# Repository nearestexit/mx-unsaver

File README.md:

# mx-unsaver

Custom keyboard and numpad inspired by vintage Cherry keyboards and the [IBM "Unsaver"](https://sharktastica.co.uk/topics/keyboard-dictionary/unsaver).
Designed in Onshape and KiCad.
Powered by [QMK](https://github.com/qmk/qmk_firmware).

## Overview
- Side profile and shape inspired by the Cherry G80-5700 and G80-1800
- PCB Top-Mount
- Integrated USB Hub with 1x USB-C Upstream port and 2x USB-C and 2x USB-A Downstream ports
- Brass through-weight

**Case Source (Onshape):** https://cad.onshape.com/documents/1d9e79a61d42e7395c429f47/w/28912f958105e1c831f67a9e/e/537bd51b2d234361e6d6eea3

## PCB
The PCB supports ISO and ANSI. Unfortunately, due to an oversight, the Case only supports ANSI enter. It could be relatively easily modified to support ISO enter.
I ordered single bare PCBs from EuroCircuits and OSHPark and hand-soldered the components, so I do not have JLCPCB production files available.

**Important: The PCB has the words "Made In Germany" printed on it. This is because it was actually manufactured in Germany. If you choose to have it manufactured in China, please remove this logo from the PCB.**

## Bill of Materials

| Item  | Quantity | Link |
| ------------- | ------------- | ------------- | 
| M2x4x3mm Hex Standoff | 2 | https://www.ebay.com/itm/355663469861?var=624766479032 |
| M2x3x4mm Wafer head Screw | 2 | https://www.ebay.com/itm/355676691340?var=624776776427 |
| Feet | 8 | https://cannonkeys.com/products/akb-feet |
| M2.5x8mm BHCS | 57 | https://mcmaster.com/92095A459 |
| M2.5x6mm SHCS | 14 | https://mcmaster.com/91292A010 |
| M2.5x10mm SHCS | 7 | https://mcmaster.com/91292A014 |
| M2.5x25mm SHCS | 6 | https://mcmaster.com/91292A036 |
| M2.5x20mm SHCS | 4 | https://mcmaster.com/91292A019 |
| M3x6mm Countersunk | 5 | https://mcmaster.com/92125A126 |
| M3x8mm Countersunk | 9 | https://mcmaster.com/92125A128 |
| 1:1 JST-SH Cable (50mm) | 3 | https://www.digikey.com/en/products/detail/adafruit-industries-llc/4210/10230021 |
| FPC Cable (50.8mm) | 1 | https://www.digikey.com/en/products/detail/molex/0151660207/3281088 |

## USB Hub
The USB Hub utilizes two [FE1.1S](https://www.digikey.ca/datasheets/production/1879844/1/FE1-1s-Datasheet.html) USB 2.0 HS Hub chips in series. It can deliver a total of 400mA downstream (the keyboard is assumed to use 100mA).

## Firmware

A QMK .bin file is provided for flashing, as well as QMK source files.

(The original Unsaver in this picture is not for sale.)

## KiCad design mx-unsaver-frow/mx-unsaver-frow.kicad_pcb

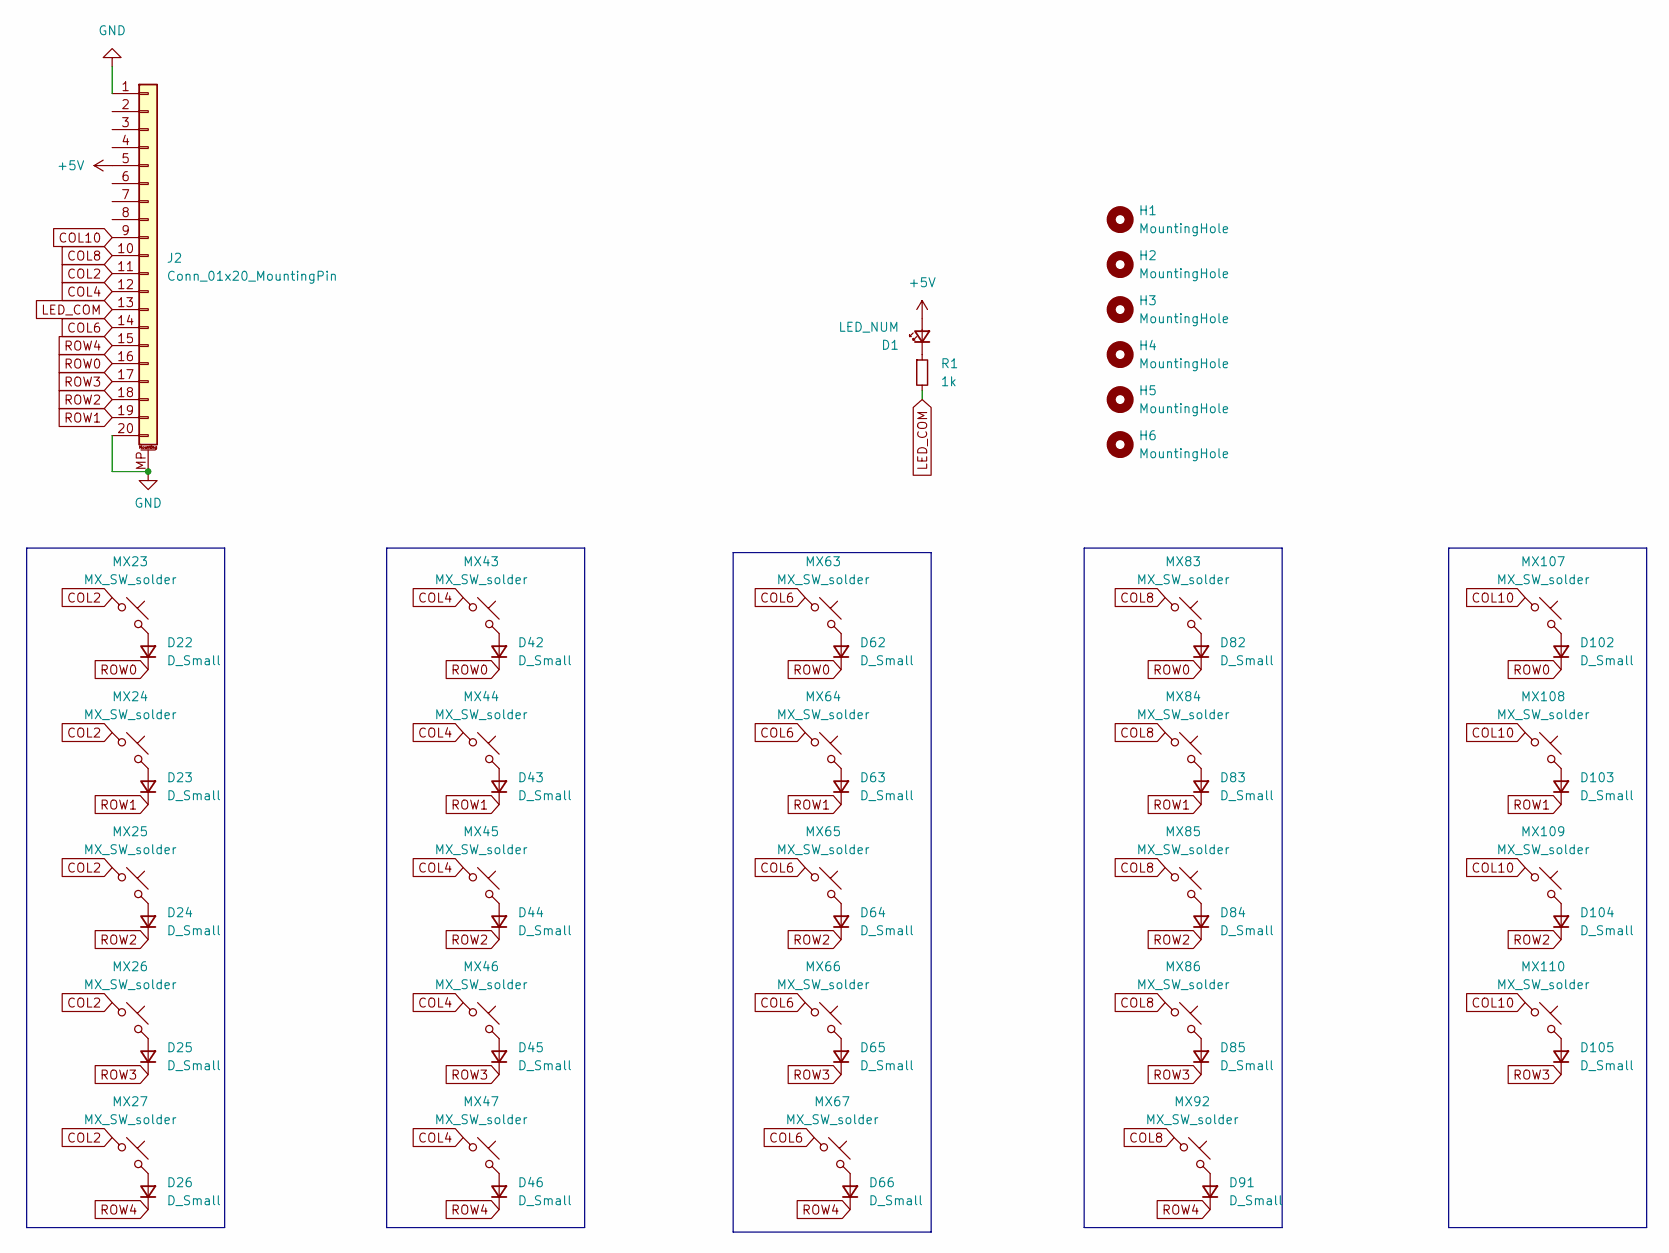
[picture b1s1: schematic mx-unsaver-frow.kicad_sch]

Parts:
D1: LED_NUM; LED_MX_3mm_Offset_Flipped; Digikey 67-1058-ND
D22, D23, D24, D25, D26, D42, D43, D44, D45, D46, D62, D63, D64, D65, D66, D82, D83, D84, D85, D91, D102, D103, D104, D105: D_Small; D_SOD-123_ShiftedSilkscreen; Digikey 1N4148W-FDICT-ND
H1, H2, H3, H4, H5, H6: MountingHole; MountingHole_2.7mm_M2.5
J2: Conn_01x20_MountingPin; CONN-SMD_20P-P0.50_10051922-2010ELF; Digikey 609-10051922-2010ELFCT-ND
MX23, MX24, MX25, MX26, MX27, MX43, MX44, MX45, MX46, MX47, MX63, MX64, MX65, MX66, MX67, MX83, MX84, MX85, MX86, MX92, MX107, MX108, MX109, MX110: MX_SW_solder; SW_MX_1u_PCBMount
R1: 1k; R_0805_2012Metric; Digikey P1.0KDACT-ND

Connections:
+5V: D1.2 (A), J2.5
COL2: J2.11, MX23.1, MX24.1, MX25.1, MX26.1, MX27.1
COL4: J2.12, MX43.1, MX44.1, MX45.1, MX46.1, MX47.1
COL6: J2.14, MX63.1, MX64.1, MX65.1, MX66.1, MX67.1
COL8: J2.10, MX83.1, MX84.1, MX85.1, MX86.1, MX92.1
COL10: J2.9, MX107.1, MX108.1, MX109.1, MX110.1
GND: J2.1, J2.20, J2.MP (MountPin)
LED_COM: J2.13, R1.2
unnamed: D1.1 (K), R1.1
unnamed: D22.2 (A), MX23.2
unnamed: D23.2 (A), MX24.2
unnamed: D24.2 (A), MX25.2
unnamed: D25.2 (A), MX26.2
unnamed: D26.2 (A), MX27.2
unnamed: D42.2 (A), MX43.2
unnamed: D43.2 (A), MX44.2
unnamed: D44.2 (A), MX45.2
unnamed: D45.2 (A), MX46.2
unnamed: D46.2 (A), MX47.2
unnamed: D62.2 (A), MX63.2
unnamed: D63.2 (A), MX64.2
unnamed: D64.2 (A), MX65.2
unnamed: D65.2 (A), MX66.2
unnamed: D66.2 (A), MX67.2
unnamed: D82.2 (A), MX83.2
unnamed: D83.2 (A), MX84.2
unnamed: D84.2 (A), MX85.2
unnamed: D85.2 (A), MX86.2
unnamed: D91.2 (A), MX92.2
unnamed: D102.2 (A), MX107.2
unnamed: D103.2 (A), MX108.2
unnamed: D104.2 (A), MX109.2
unnamed: D105.2 (A), MX110.2
ROW0: D22.1 (K), D42.1 (K), D62.1 (K), D82.1 (K), D102.1 (K), J2.16
ROW1: D23.1 (K), D43.1 (K), D63.1 (K), D83.1 (K), D103.1 (K), J2.19
ROW2: D24.1 (K), D44.1 (K), D64.1 (K), D84.1 (K), D104.1 (K), J2.18
ROW3: D25.1 (K), D45.1 (K), D65.1 (K), D85.1 (K), D105.1 (K), J2.17
ROW4: D26.1 (K), D46.1 (K), D66.1 (K), D91.1 (K), J2.15

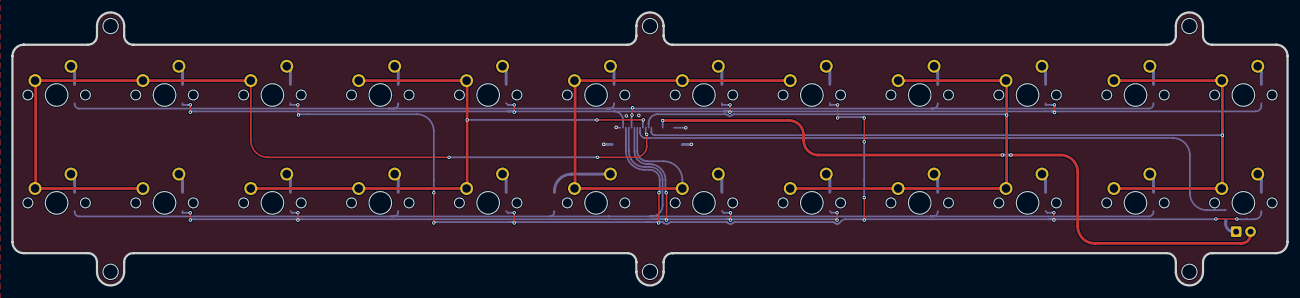
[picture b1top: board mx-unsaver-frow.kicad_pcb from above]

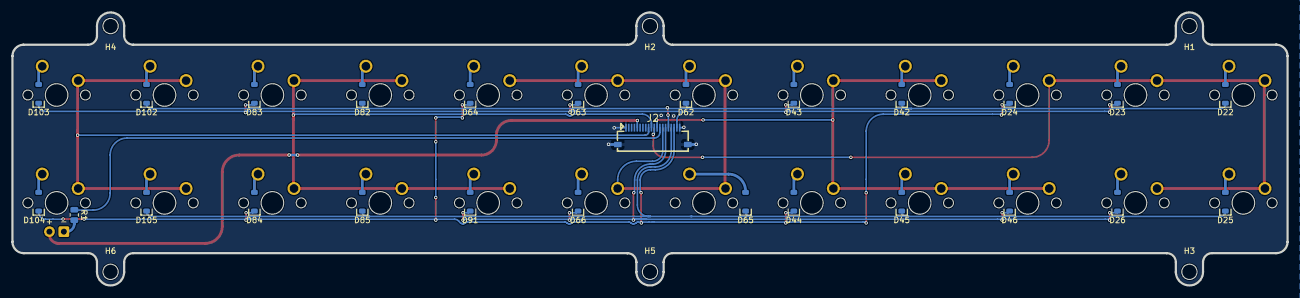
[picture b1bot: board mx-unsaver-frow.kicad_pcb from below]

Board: 2 copper layers, 225.2 x 48.2 mm, 57 parts (33 on the bottom side), 38 nets.

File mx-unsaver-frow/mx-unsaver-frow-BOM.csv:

"Reference","Value","Datasheet","Footprint","Qty","DNP","Digikey"
"D1","LED_NUM","~","mx-unsaver:LED_MX_3mm_Offset_Flipped","1","","67-1058-ND"
"D22,D23,D24,D25,D26,D42,D43,D44,D45,D46,D62,D63,D64,D65,D66,D82,D83,D84,D85,D91,D102,D103,D104,D105","D_Small","~","mx-unsaver:D_SOD-123_ShiftedSilkscreen","24","","1N4148W-FDICT-ND"
"J2","Conn_01x20_MountingPin","~","mx-unsaver:CONN-SMD_20P-P0.50_10051922-2010ELF","1","","609-10051922-2010ELFCT-ND"
"MX23,MX24,MX25,MX26,MX27,MX43,MX44,MX45,MX46,MX47,MX63,MX64,MX65,MX66,MX67,MX83,MX84,MX85,MX86,MX92,MX107,MX108,MX109,MX110","MX_SW_solder","~","mx-unsaver:SW_MX_1u_PCBMount","24","",""
"R1","1k","~","Resistor_SMD:R_0805_2012Metric","1","","P1.0KDACT-ND"

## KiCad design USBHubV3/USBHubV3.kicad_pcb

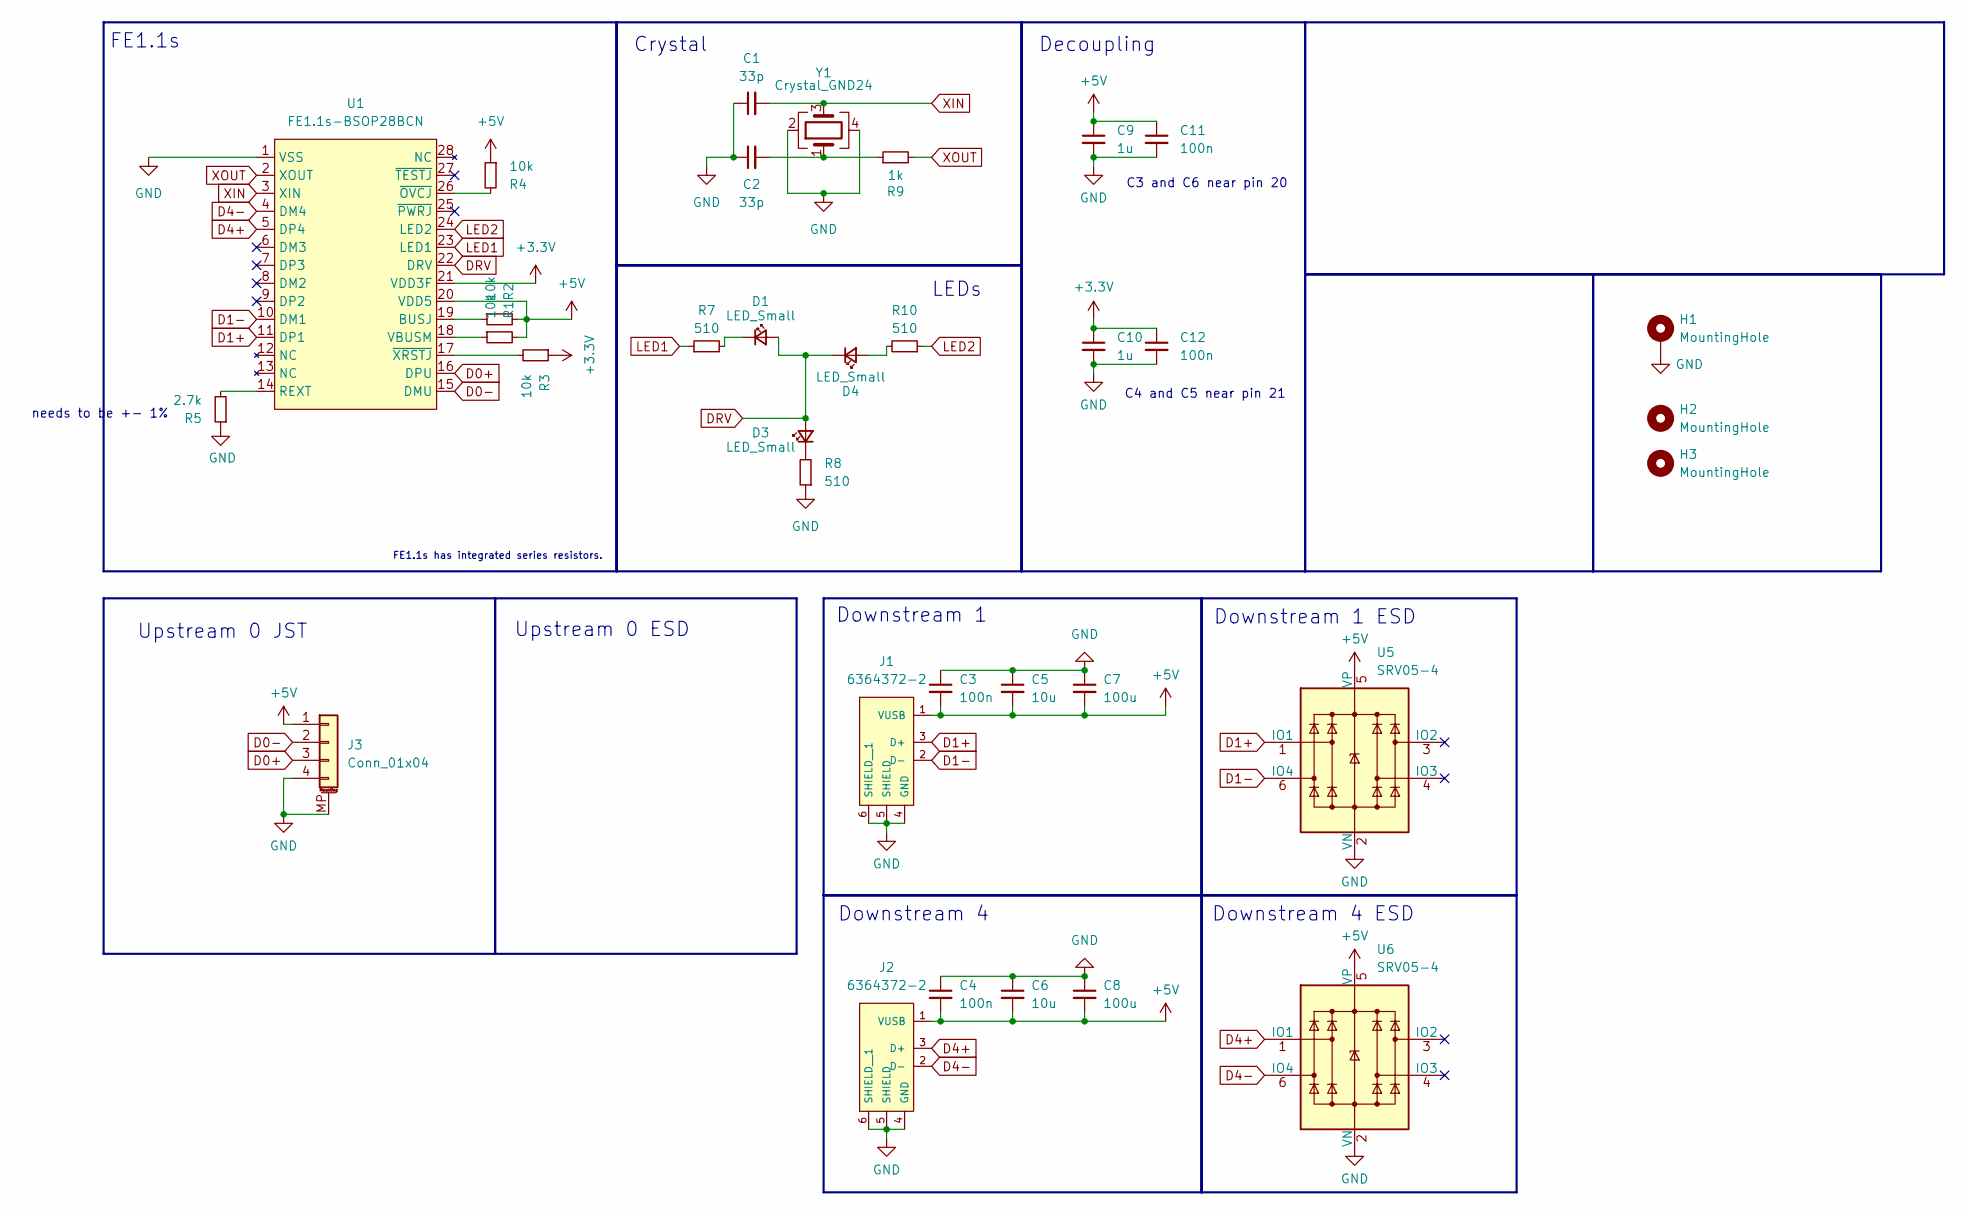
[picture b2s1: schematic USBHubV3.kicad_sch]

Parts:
C1, C2: 33p; C_0603_1608Metric; Digikey 1276-1070-1-ND
C3, C4, C11, C12: 100n; C_0603_1608Metric; Digikey 311-1088-1-ND
C5, C6: 10u; C_0603_1608Metric; Digikey 1276-1192-1-ND
C7, C8: 100u; C_1206_3216Metric; Digikey 490-GRM31CR60J107KEA8LCT-ND
C9, C10: 1u; C_0603_1608Metric; Digikey 1276-6524-1-ND
D1, D3, D4: LED_Small; LED_0603_1608Metric; Digikey 2007-BL-HJC36G-AV-TRBCT-ND
H1: MountingHole; MountingHole_2.7mm_M2.5_DIN965_Pad
H2, H3: MountingHole; MountingHole_2.7mm_M2.5
J1, J2: 6364372-2; TE_6364372-2; Digikey A122647-ND
J3: Conn_01x04; JST_SH_SM04B-SRSS-TB_1x04-1MP_P1.00mm_Horizontal; Digikey 455-SM04B-SRSS-TBCT-ND
R1, R2, R3, R4: 10k; R_0603_1608Metric; Digikey 311-10.0KHRCT-ND
R5: 2.7k; R_0603_1608Metric; Digikey RMCF0603FT2K70CT-ND
R7, R8, R10: 510; R_0603_1608Metric; Digikey RR08P510DCT-ND
R9: 1k; R_0603_1608Metric; Digikey RMCF0603FT1K00CT-ND
U1: FE1.1s-BSOP28BCN; SSOP-28_3.9x9.9mm_P0.635mm
U5, U6: SRV05-4; SOT-23-6-routable; Digikey 5399-SRV05-4CT-ND
Y1: Crystal_GND24; Crystal_SMD_3225-4Pin_3.2x2.5mm; Digikey XC1810CT-ND

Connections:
+3.3V: C10.1, C12.1, R3.1, U1.21 (VDD3F)
+5V: C3.2, C4.2, C5.2, C6.2, C7.2, C8.2, C9.1, C11.1, J1.1 (VUSB), J2.1 (VUSB), J3.1, R1.2, R2.2, R4.1, U1.20 (VDD5), U5.5 (VP), U6.5 (VP)
D0+: J3.3, U1.16 (DPU)
D0-: J3.2, U1.15 (DMU)
D1+: J1.3 (D+), U1.11 (DP1), U5.1 (IO1)
D1-: J1.2 (D-), U1.10 (DM1), U5.6 (IO4)
D4+: J2.3 (D+), U1.5 (DP4), U6.1 (IO1)
D4-: J2.2 (D-), U1.4 (DM4), U6.6 (IO4)
DRV: D1.2 (A), D3.2 (A), D4.1 (K), U1.22 (DRV)
GND: C1.1, C2.1, C3.1, C4.1, C5.1, C6.1, C7.1, C8.1, C9.2, C10.2, C11.2, C12.2, H1.1, J1.4 (GND), J1.5 (SHIELD), J1.6 (SHIELD__1), J2.4 (GND), J2.5 (SHIELD), J2.6 (SHIELD__1), J3.4, J3.MP (MountPin), R5.1, R8.1, U1.1 (VSS), U5.2 (VN), U6.2 (VN), Y1.2, Y1.4
LED1: R7.1, U1.23 (LED1)
LED2: R10.1, U1.24 (LED2)
unnamed: C2.2, R9.1, Y1.1
unnamed: D1.1 (K), R7.2
unnamed: D3.1 (K), R8.2
unnamed: D4.2 (A), R10.2
unnamed: R2.1, U1.19 (BUSJ)
unnamed: R5.2, U1.14 (REXT)
unnamed: R1.1, U1.18 (VBUSM)
unnamed: R4.2, U1.26 (~OVCJ)
unnamed: R3.2, U1.17 (~XRSTJ)
XIN: C1.2, U1.3 (XIN), Y1.3
XOUT: R9.2, U1.2 (XOUT)

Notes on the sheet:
Upstream 0 JST
Decoupling
Upstream 0 ESD
Downstream 4
FE1.1s
C4 and C5 near pin 21
FE1.1s has integrated series resistors.
LEDs
Downstream 1
Downstream 1 ESD
C3 and C6 near pin 20
Crystal
needs to be +- 1%
Downstream 4 ESD

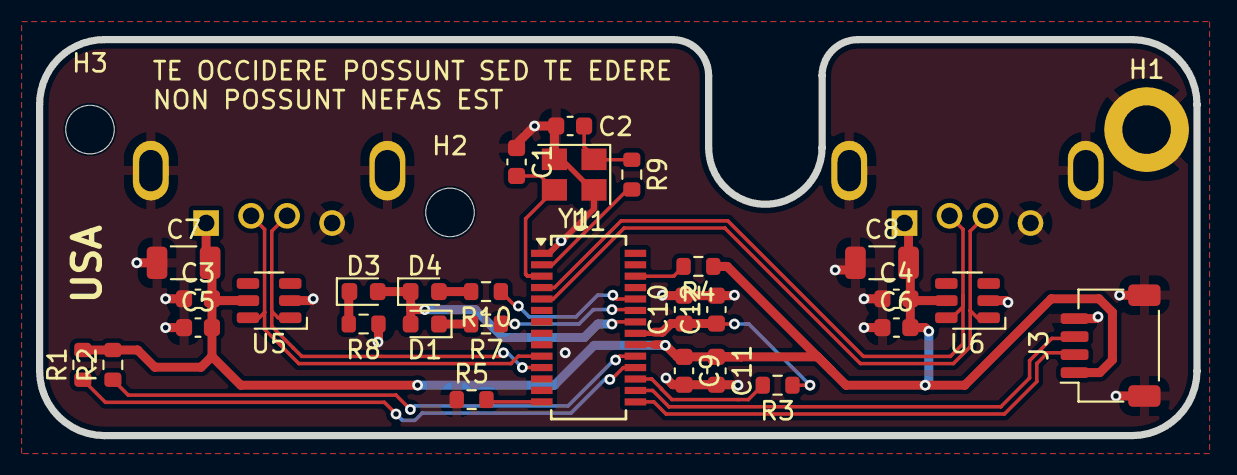
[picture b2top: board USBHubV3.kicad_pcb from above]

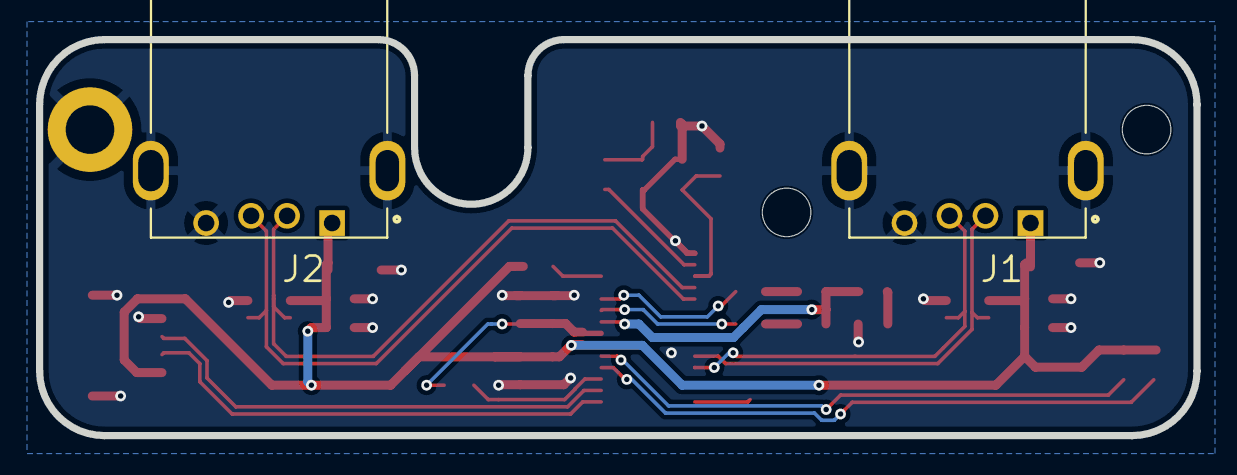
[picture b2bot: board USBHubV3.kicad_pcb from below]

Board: 2 copper layers, 64.3 x 22.0 mm, 34 parts (2 on the bottom side), 23 nets.

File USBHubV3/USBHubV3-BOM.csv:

Reference,Value,Datasheet,Footprint,Qty,DNP,Digikey
"C1,C2",33p,~,Capacitor_SMD:C_0603_1608Metric,2,,1276-1070-1-ND
"C3,C4,C11,C12",100n,~,Capacitor_SMD:C_0603_1608Metric,4,,311-1088-1-ND
"C5,C6",10u,~,Capacitor_SMD:C_0603_1608Metric,2,,1276-1192-1-ND
"C7,C8",100u,~,Capacitor_SMD:C_1206_3216Metric,2,,490-GRM31CR60J107KEA8LCT-ND
"C9,C10",1u,~,Capacitor_SMD:C_0603_1608Metric,2,,1276-6524-1-ND
"D1,D3,D4",LED_Small,~,LED_SMD:LED_0603_1608Metric,3,,2007-BL-HJC36G-AV-TRBCT-ND
"J1,J2",6364372-2,,TE_6364372-2,2,,  A122647-ND
J3,Conn_01x04,~,Connector_JST:JST_SH_SM04B-SRSS-TB_1x04-1MP_P1.00mm_Horizontal,1,,455-SM04B-SRSS-TBCT-ND
"R1,R2,R3,R4",10k,~,Resistor_SMD:R_0603_1608Metric,4,,311-10.0KHRCT-ND
R5,2.7k,~,Resistor_SMD:R_0603_1608Metric,1,,RMCF0603FT2K70CT-ND
"R7,R8,R10",510,~,Resistor_SMD:R_0603_1608Metric,3,,RR08P510DCT-ND
R9,1k,~,Resistor_SMD:R_0603_1608Metric,1,,RMCF0603FT1K00CT-ND
U1,FE1.1s-BSOP28BCN,https://www.lcsc.com/datasheet/C9359.pdf,Package_SO:SSOP-28_3.9x9.9mm_P0.635mm,1,,
"U5,U6",SRV05-4,http://www.onsemi.com/pub/Collateral/SRV05-4-D.PDF,PCM_marbastlib-various:SOT-23-6-routable,2,,5399-SRV05-4CT-ND
Y1,Crystal_GND24,~,Crystal:Crystal_SMD_3225-4Pin_3.2x2.5mm,1,,XC1810CT-ND

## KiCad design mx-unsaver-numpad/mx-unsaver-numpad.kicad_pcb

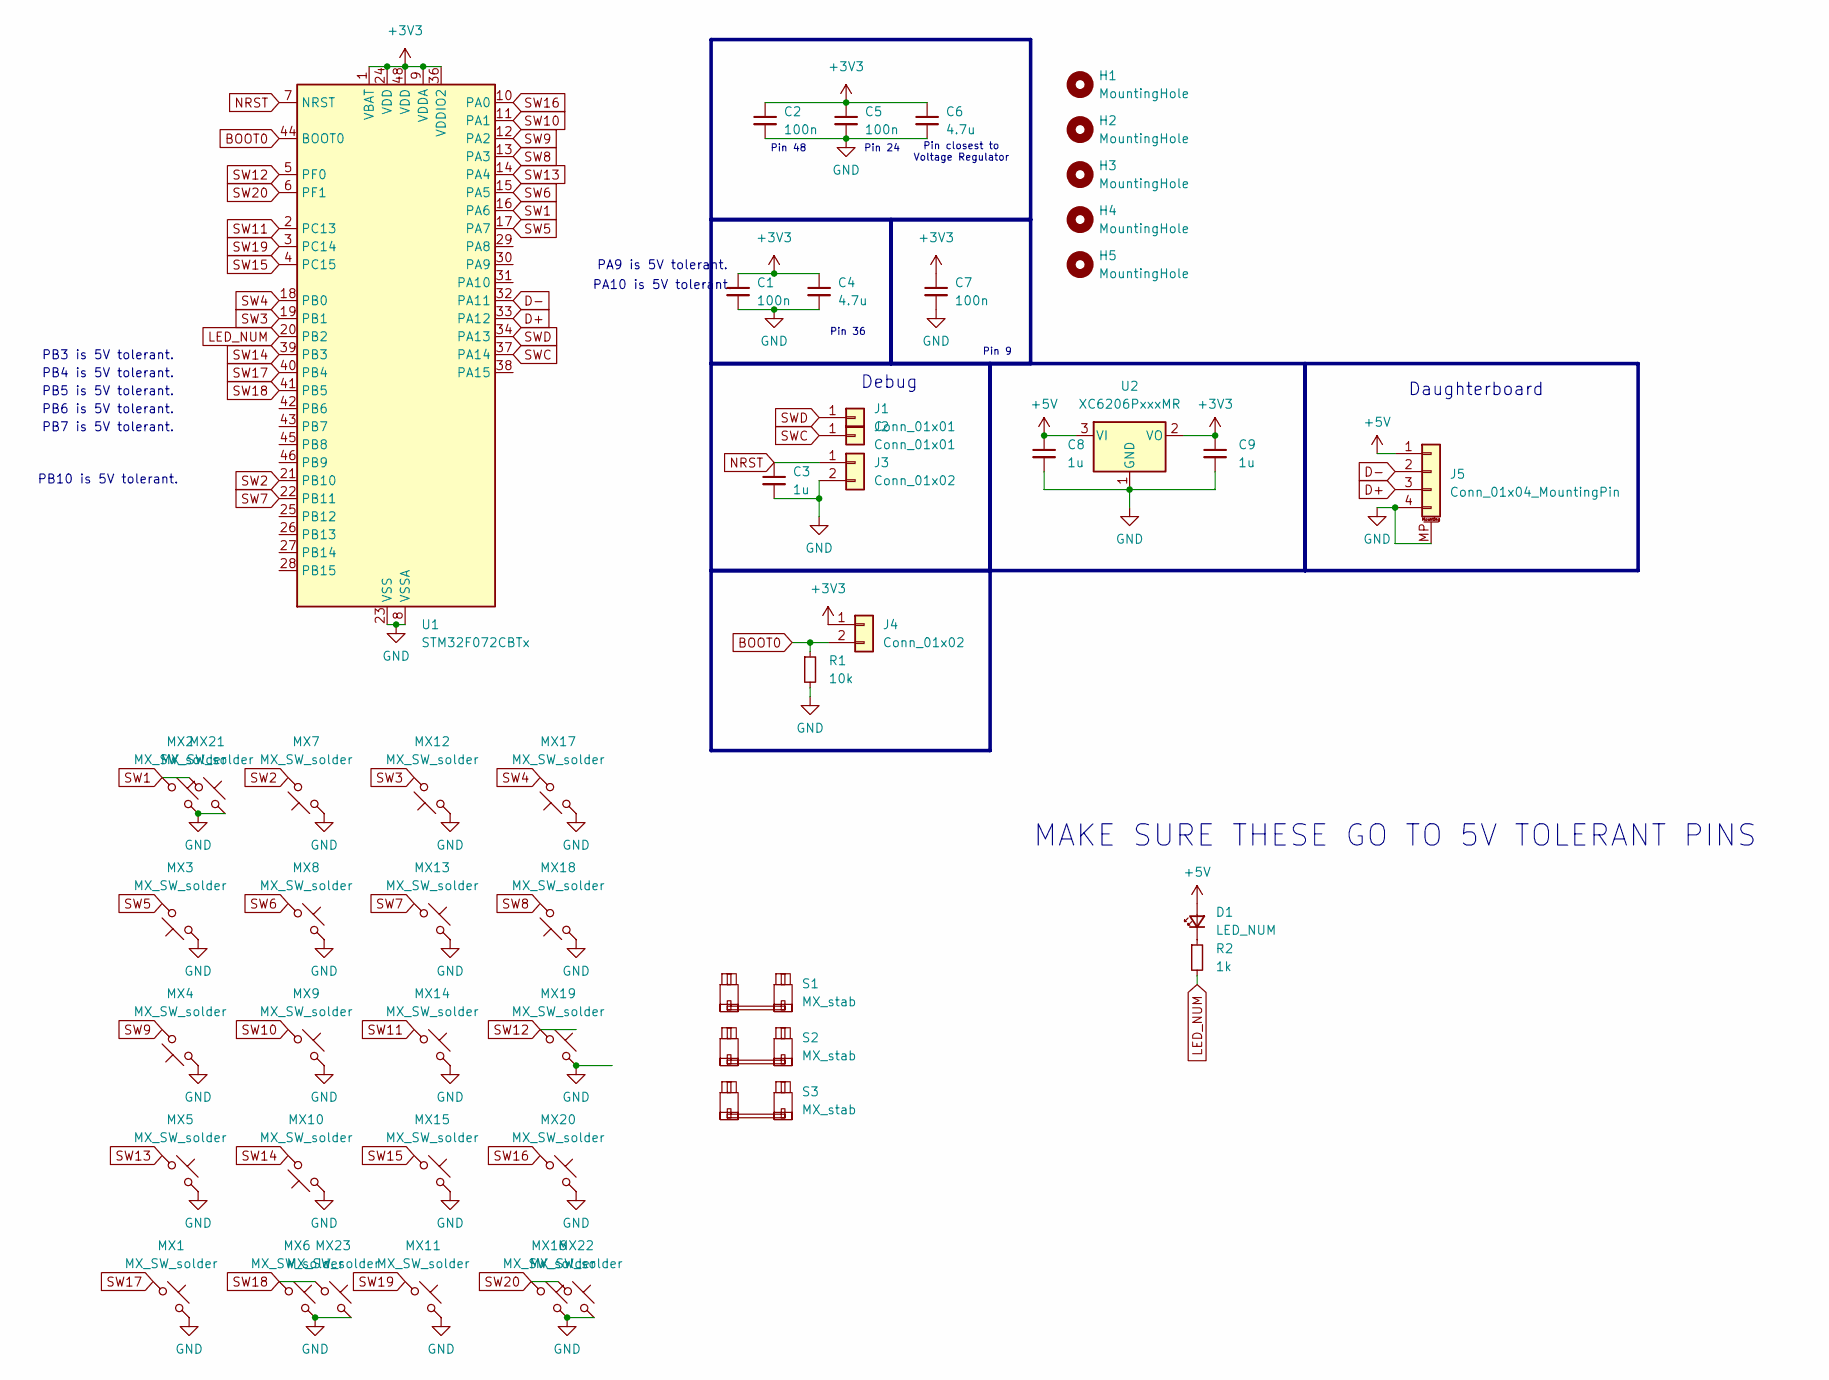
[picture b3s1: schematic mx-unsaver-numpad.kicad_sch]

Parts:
C1, C2, C5, C7: 100n; C_0603_1608Metric; Digikey 311-1088-1-ND
C3, C8, C9: 1u; C_0805_2012Metric; Digikey 1276-1029-1-ND
C4, C6: 4.7u; C_0603_1608Metric; Digikey 1276-1784-1-ND
D1: LED_NUM; LED_MX_3mm_Offset_Flipped; Digikey 67-1058-ND
H1, H2, H3, H4: MountingHole; MountingHole_2.7mm_M2.5
H5: MountingHole; HOLE_BackSpace_Slots
J1, J2: Conn_01x01; PinHeader_1x01_P2.54mm
J3, J4: Conn_01x02; PinHeader_1x02_P2.54mm_BOOT
J5: Conn_01x04_MountingPin; JST_SH_SM04B-SRSS-TB_1x04-1MP_P1.00mm_Horizontal; Digikey 455-SM04B-SRSS-TBCT-ND
MX1, MX3, MX4, MX5, MX6, MX7, MX9, MX10, MX11, MX12, MX13, MX14, MX15, MX16, MX17, MX18, MX19, MX20, MX22, MX23: MX_SW_solder; SW_MX_1u_PCBMount
MX2: MX_SW_solder; SW_MX_1u_PCBMount_NoRight
MX8: MX_SW_solder; SW_MX_1u_PCBMount_NoLeft
MX21: MX_SW_solder; SW_MX_1u_3pin
R1: 10k; R_0805_2012Metric; Digikey RMCF0805FT10K0CT-ND
R2: 1k; R_0805_2012Metric; Digikey P1.0KDACT-ND
S1, S2, S3: MX_stab; STAB_MX_2u_FixedDistance
U1: STM32F072CBTx; LQFP-48_7x7mm_P0.5mm
U2: XC6206PxxxMR; SOT-23-3; Digikey 893-XC6206P332MR-GCT-ND

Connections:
+3V3: C1.1, C2.1, C4.1, C5.1, C6.1, C7.1, C9.1, J4.1, U1.1 (VBAT), U1.9 (VDDA), U1.24 (VDD), U1.36 (VDDIO2), U1.48 (VDD), U2.2 (VO)
+5V: C8.1, D1.2 (A), J5.1, U2.3 (VI)
BOOT0: J4.2, R1.1, U1.44 (BOOT0)
D+: J5.3, U1.33 (PA12)
D-: J5.2, U1.32 (PA11)
GND: C1.2, C2.2, C3.2, C4.2, C5.2, C6.2, C7.2, C8.2, C9.2, J3.2, J5.4, J5.MP (MountPin), MX1.2, MX2.2, MX3.1, MX4.1, MX5.2, MX6.2, MX7.1, MX8.2, MX9.2, MX10.1, MX11.2, MX12.1, MX13.2, MX14.2, MX15.2, MX16.2, MX17.1, MX18.1, MX19.2, MX20.2, MX21.2, MX22.2, MX23.2, R1.2, U1.8 (VSSA), U1.23 (VSS), U1.35 (VSS), U1.47 (VSS), U2.1 (GND)
LED_NUM: R2.2, U1.20 (PB2)
NRST: C3.1, J3.1, U1.7 (NRST)
unnamed: D1.1 (K), R2.1
SW1: MX2.1, MX21.1, U1.16 (PA6)
SW2: MX7.2, U1.21 (PB10)
SW3: MX12.2, U1.19 (PB1)
SW4: MX17.2, U1.18 (PB0)
SW5: MX3.2, U1.17 (PA7)
SW6: MX8.1, U1.15 (PA5)
SW7: MX13.1, U1.22 (PB11)
SW8: MX18.2, U1.13 (PA3)
SW9: MX4.2, U1.12 (PA2)
SW10: MX9.1, U1.11 (PA1)
SW11: MX14.1, U1.2 (PC13)
SW12: MX19.1, U1.5 (PF0)
SW13: MX5.1, U1.14 (PA4)
SW14: MX10.2, U1.39 (PB3)
SW15: MX15.1, U1.4 (PC15)
SW16: MX20.1, U1.10 (PA0)
SW17: MX1.1, U1.40 (PB4)
SW18: MX6.1, MX23.1, U1.41 (PB5)
SW19: MX11.1, U1.3 (PC14)
SW20: MX16.1, MX22.1, U1.6 (PF1)
SWC: J2.1, U1.37 (PA14)
SWD: J1.1, U1.34 (PA13)

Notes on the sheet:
PA10 is 5V tolerant.
MAKE SURE THESE GO TO 5V TOLERANT PINS
PB10 is 5V tolerant.
Pin 24
PB6 is 5V tolerant.
Debug
Pin 48
Pin 36
PB5 is 5V tolerant.
PB3 is 5V tolerant.
Pin 9
Daughterboard
Pin closest to Voltage Regulator
PB4 is 5V tolerant.
PB7 is 5V tolerant.
PA9 is 5V tolerant.

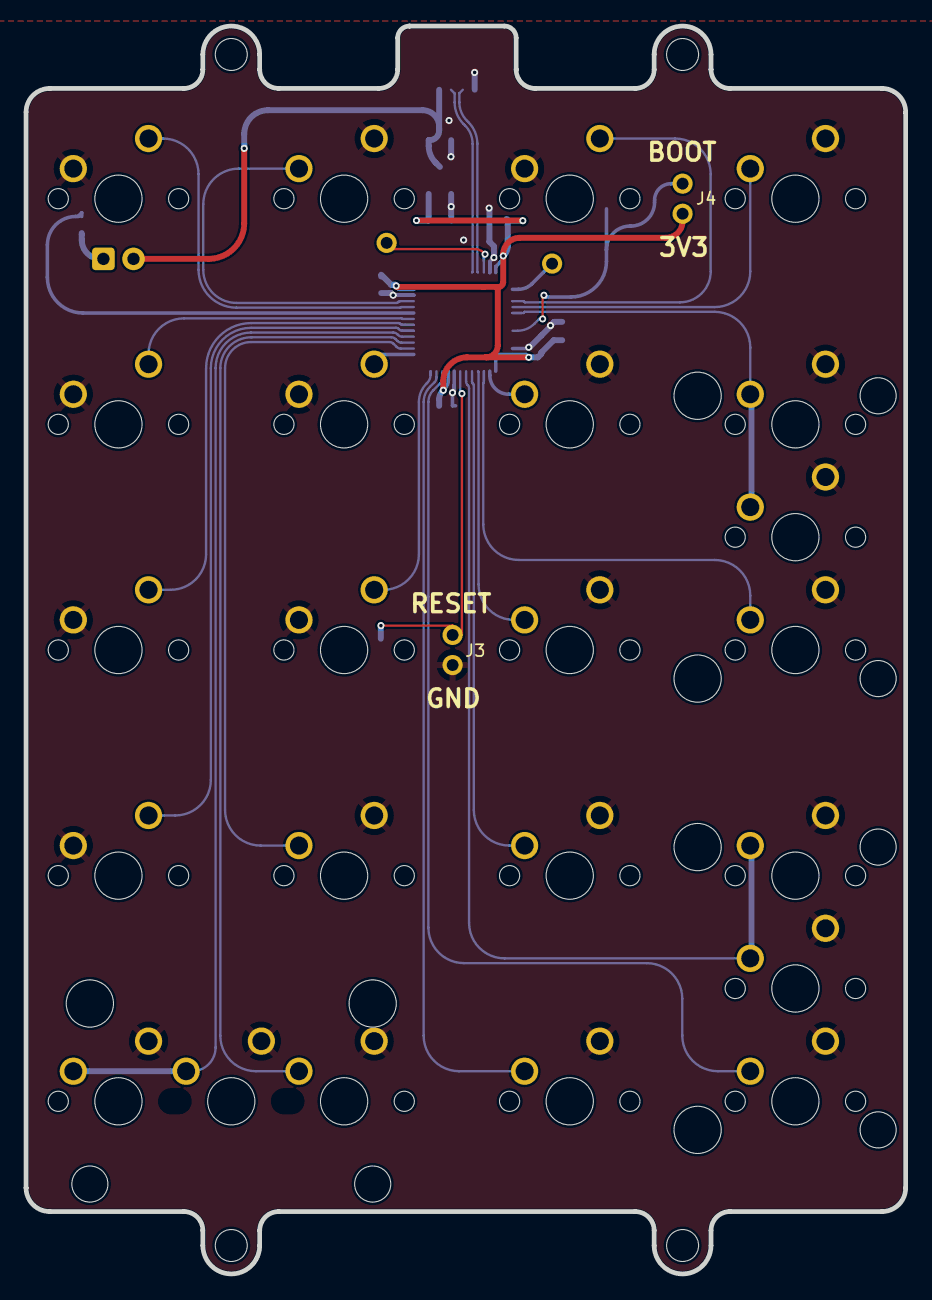
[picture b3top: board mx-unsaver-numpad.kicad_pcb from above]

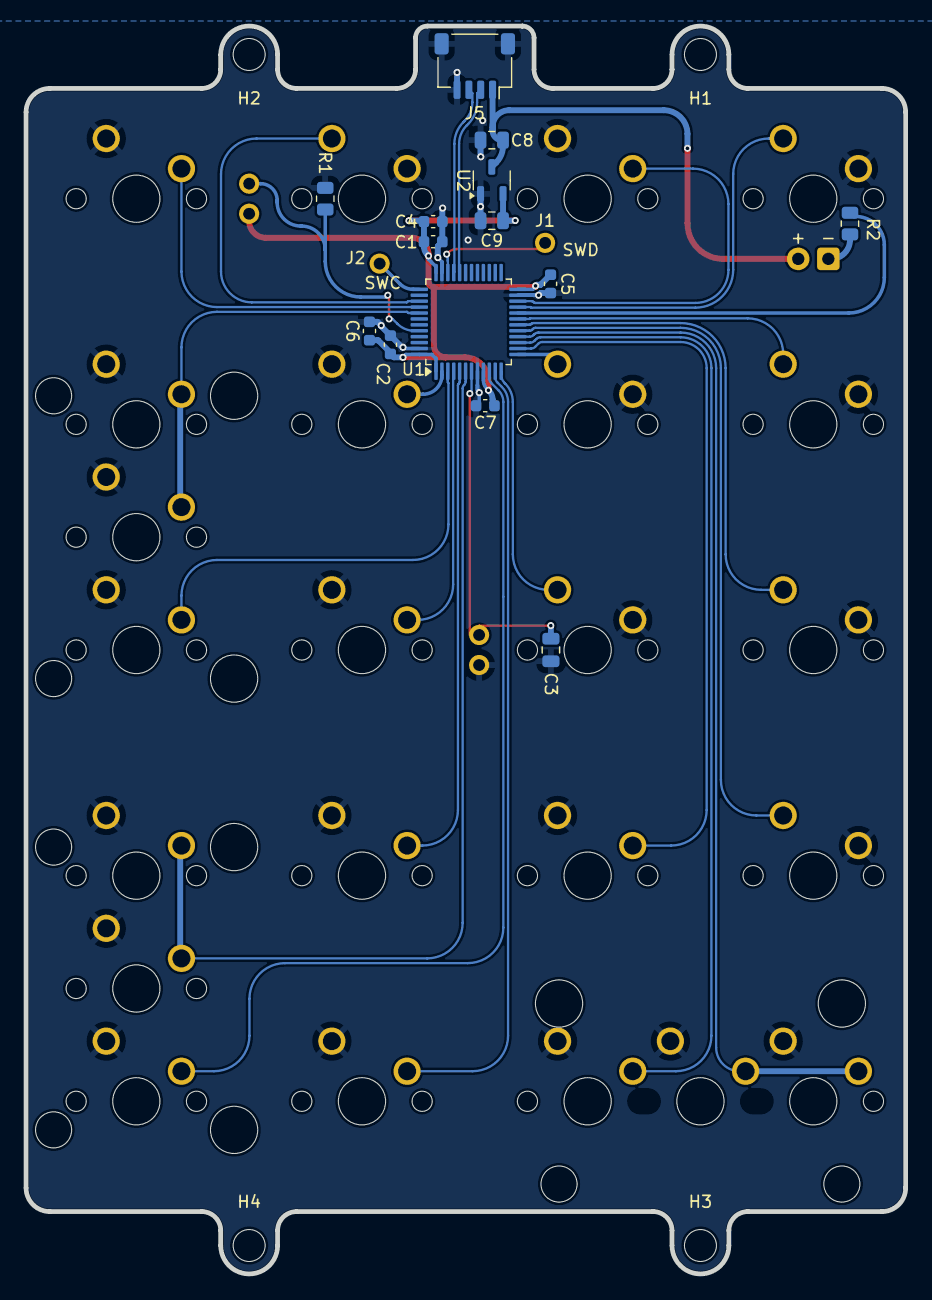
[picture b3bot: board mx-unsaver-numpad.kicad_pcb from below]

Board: 2 copper layers, 74.3 x 105.3 mm, 50 parts (21 on the bottom side), 31 nets.

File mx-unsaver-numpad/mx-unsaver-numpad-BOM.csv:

Reference,Value,Datasheet,Footprint,Qty,DNP,Digikey
"C1,C2,C5,C7",100n,~,Capacitor_SMD:C_0603_1608Metric,4,,311-1088-1-ND
"C3,C8,C9",1u,~,Capacitor_SMD:C_0805_2012Metric,3,,1276-1029-1-ND
"C4,C6",4.7u,~,Capacitor_SMD:C_0603_1608Metric,2,,1276-1784-1-ND
D1,LED_NUM,~,mx-unsaver:LED_MX_3mm_Offset_Flipped,1,,67-1058-ND
"J1,J2",Conn_01x01,~,mx-unsaver:PinHeader_1x01_P2.54mm,2,,
"J3,J4",Conn_01x02,~,mx-unsaver:PinHeader_1x02_P2.54mm_BOOT,2,,
J5,Conn_01x04_MountingPin,~,Connector_JST:JST_SH_SM04B-SRSS-TB_1x04-1MP_P1.00mm_Horizontal,1,,455-SM04B-SRSS-TBCT-ND
"MX1,MX2,MX3,MX4,MX5,MX6,MX7,MX8,MX9,MX10,MX11,MX12,MX13,MX14,MX15,MX16,MX17,MX18,MX19,MX20,MX21,MX22,MX23",MX_SW_solder,~,-- mixed values --,23,,
R1,10k,~,Resistor_SMD:R_0805_2012Metric,1,,RMCF0805FT10K0CT-ND
R2,1k,~,Resistor_SMD:R_0805_2012Metric,1,,P1.0KDACT-ND
"S1,S2,S3",MX_stab,,mx-unsaver:STAB_MX_2u_FixedDistance,3,,
U1,STM32F072CBTx,https://www.st.com/resource/en/datasheet/stm32f072cb.pdf,Package_QFP:LQFP-48_7x7mm_P0.5mm,1,,
U2,XC6206PxxxMR,https://www.torexsemi.com/file/xc6206/XC6206.pdf,Package_TO_SOT_SMD:SOT-23-3,1,,893-XC6206P332MR-GCT-ND

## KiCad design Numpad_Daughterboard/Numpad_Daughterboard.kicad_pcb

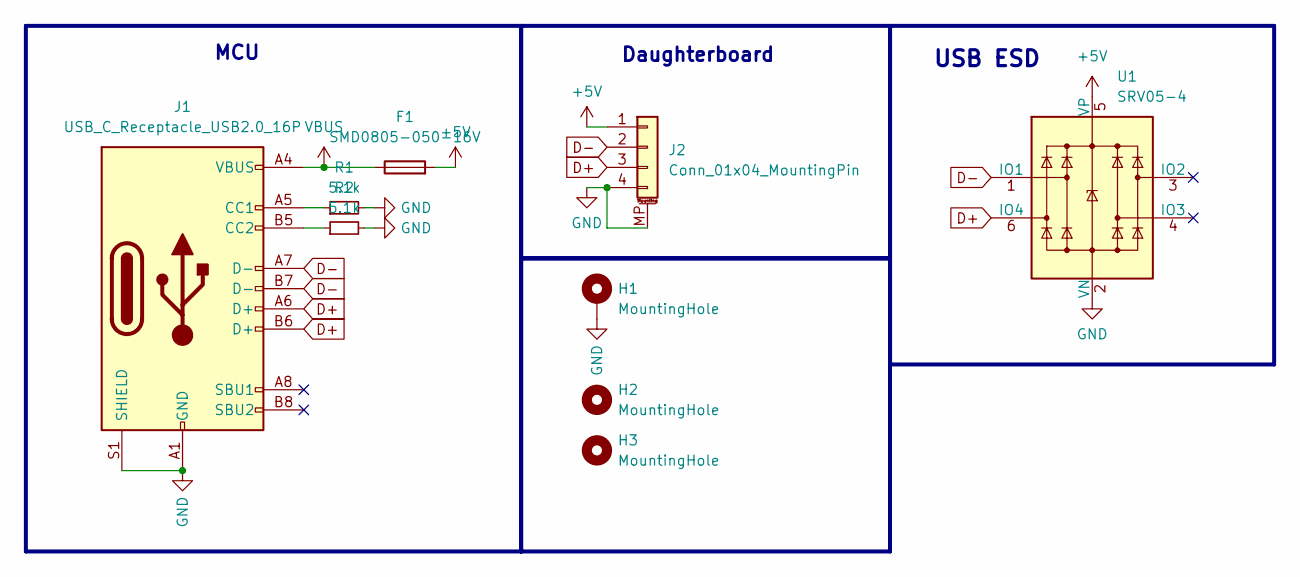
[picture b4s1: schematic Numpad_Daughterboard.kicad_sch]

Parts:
F1: SMD0805-050-16V; Fuse_1206_3216Metric; Manufacturer Part Number SMD0805-050-16V; LCSC Part Number C2833485
H1: MountingHole; MountingHole_2.5mm_Pad
H2, H3: MountingHole; MountingHole_2.7mm_M2.5
J1: USB_C_Receptacle_USB2.0_16P; PHOENIX_1332645; Digikey 277-1332645CT-ND
J2: Conn_01x04_MountingPin; JST_SH_SM04B-SRSS-TB_1x04-1MP_P1.00mm_Horizontal; Digikey 455-SM04B-SRSS-TBCT-ND
R1, R2: 5.1k; C_0603_1608Metric_Pad1.08x0.95mm_HandSolder; Digikey P5.10KHCT-ND
U1: SRV05-4; SOT-23-6-routable; Digikey 5399-SRV05-4CT-ND

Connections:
+5V: F1.2, J2.1, U1.5 (VP)
D+: J1.A6 (D+), J1.B6 (D+), J2.3, U1.6 (IO4)
D-: J1.A7 (D-), J1.B7 (D-), J2.2, U1.1 (IO1)
GND: H1.1, J1.A1 (GND), J1.A12 (GND), J1.B1 (GND), J1.B12 (GND), J1.S1 (SHIELD), J2.4, J2.MP (MountPin), R1.2, R2.2, U1.2 (VN)
unnamed: J1.A5 (CC1), R1.1
unnamed: J1.B5 (CC2), R2.1
VBUS: F1.1, J1.A4 (VBUS), J1.A9 (VBUS), J1.B4 (VBUS), J1.B9 (VBUS)

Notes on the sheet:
MCU
USB ESD
Daughterboard

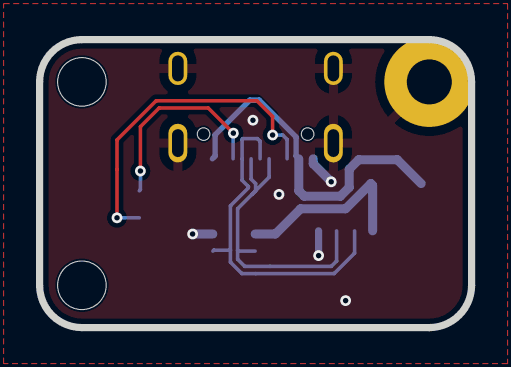
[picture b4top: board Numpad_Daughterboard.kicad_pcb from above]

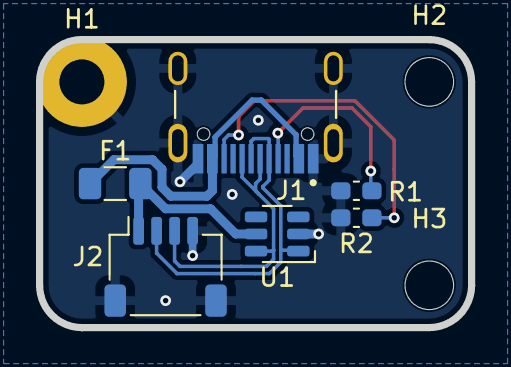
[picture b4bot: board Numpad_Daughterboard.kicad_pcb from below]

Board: 2 copper layers, 24.0 x 16.0 mm, 9 parts (9 on the bottom side), 7 nets.

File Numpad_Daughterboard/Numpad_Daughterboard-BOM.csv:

Reference,Value,Datasheet,Footprint,Qty,DNP,Digikey
F1,SMD0805-050-16V,~,Fuse:Fuse_1206_3216Metric,1,,18-1206L050/24WRCT-ND
J1,USB_C_Receptacle_USB2.0_16P,https://www.usb.org/sites/default/files/documents/usb_type-c.zip,mx-unsaver:PHOENIX_1332645,1,,277-1332645CT-ND
J2,Conn_01x04_MountingPin,~,Connector_JST:JST_SH_SM04B-SRSS-TB_1x04-1MP_P1.00mm_Horizontal,1,,455-SM04B-SRSS-TBCT-ND
"R1,R2",5.1k,~,Capacitor_SMD:C_0603_1608Metric_Pad1.08x0.95mm_HandSolder,2,,P5.10KHCT-ND
U1,SRV05-4,http://www.onsemi.com/pub/Collateral/SRV05-4-D.PDF,PCM_marbastlib-various:SOT-23-6-routable,1,,5399-SRV05-4CT-ND
